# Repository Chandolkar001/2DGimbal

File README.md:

##  2DGimbal:

### Introduction
<p align="justify">This GitHub repository showcases a remarkable 3D-printed gimbal designed specifically for mobile photography enthusiasts. The gimbal's body is crafted using innovative 3D printing technology, resulting in a lightweight and durable structure. Additionally, the repository highlights an in-house developed PCB board, engineered to provide optimal performance and seamless integration with the gimbal system. Delve into the repository to access detailed resources, including 3D printing files, PCB design specifications, and code samples, empowering you to construct your own customized mobile photography gimbal with ease. Capture stunning, shake-free visuals using this impressive blend of 3D printing and PCB technology.</p>

### Block diagram
<br>
<p align="center"></img></p>

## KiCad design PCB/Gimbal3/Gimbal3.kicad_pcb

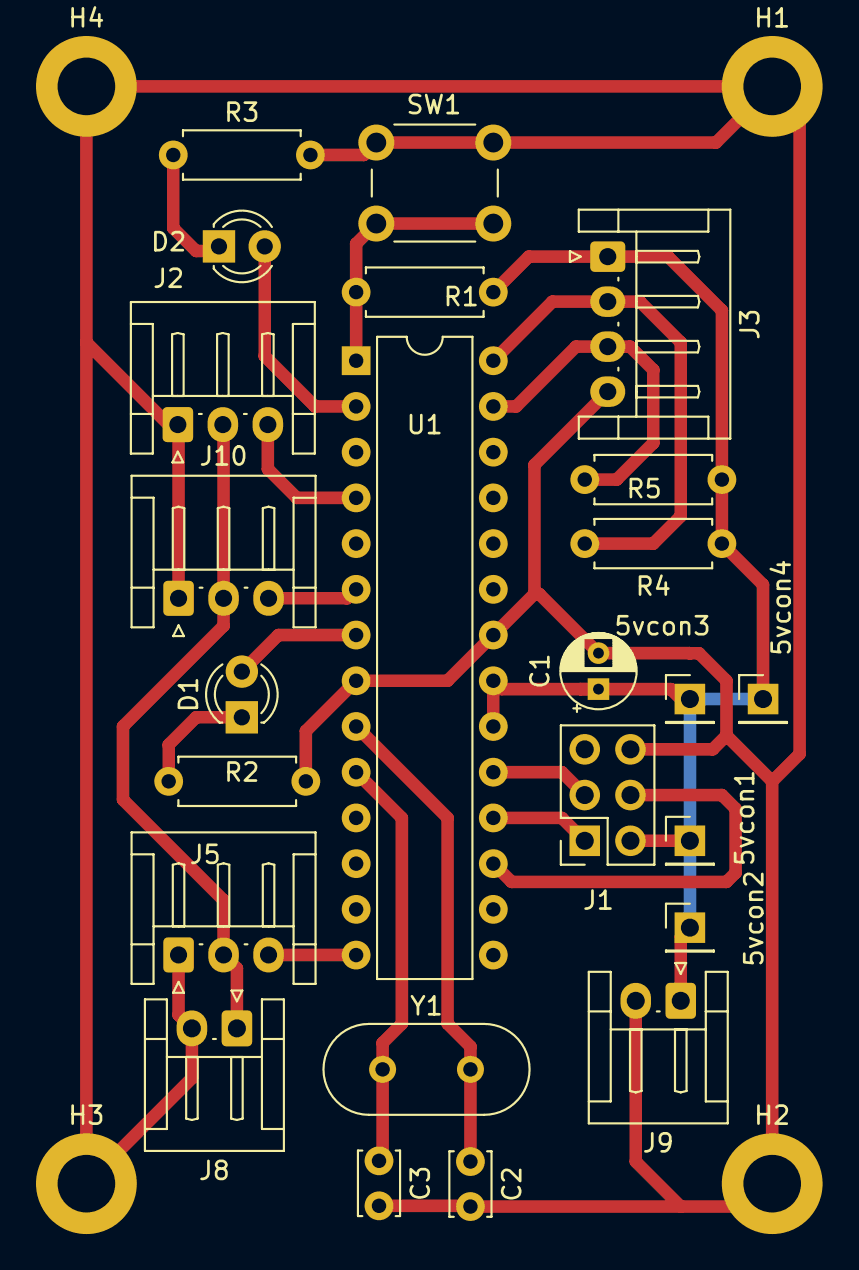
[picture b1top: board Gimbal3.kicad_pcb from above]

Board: 2 copper layers, 28 parts (0 on the bottom side), 16 nets.

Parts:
5vcon1, 5vcon2, 5vcon3, 5vcon4: Conn_01x01_Pin; PinHeader_1x01_P2.54mm_Vertical
C1: 10uF; CP_Radial_D4.0mm_P2.00mm
C2, C3: 22pF; C_Disc_D3.4mm_W2.1mm_P2.50mm
D1: POWER; LED_D3.0mm
D2: BUILD-IN; LED_D3.0mm
H1, H2, H3, H4: M3; MountingHole_3.2mm_M3_DIN965_Pad
J1: ISP; PinSocket_2x03_P2.54mm_Vertical
J2: Servo_M1; JST_EH_S3B-EH_1x03_P2.50mm_Horizontal
J3: I2C; JST_EH_S4B-EH_1x04_P2.50mm_Horizontal
J5: Servo_M2; JST_EH_S3B-EH_1x03_P2.50mm_Horizontal
J8: servo_power; JST_EH_S2B-EH_1x02_P2.50mm_Horizontal
J9: atmega_power; JST_EH_S2B-EH_1x02_P2.50mm_Horizontal
J10: Servo_M3; JST_EH_S3B-EH_1x03_P2.50mm_Horizontal
R1: 10K; R_Axial_DIN0207_L6.3mm_D2.5mm_P7.62mm_Horizontal
R2: 1K; R_Axial_DIN0207_L6.3mm_D2.5mm_P7.62mm_Horizontal
R3: 470E; R_Axial_DIN0207_L6.3mm_D2.5mm_P7.62mm_Horizontal
R4, R5: 4.7K; R_Axial_DIN0207_L6.3mm_D2.5mm_P7.62mm_Horizontal
SW1: reset; SW_PUSH_6mm
U1: ATmega328-P; DIP-28_W7.62mm
Y1: 16Mhz; Crystal_HC49-4H_Vertical

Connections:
+5V: 5vcon1.1, 5vcon2.1, 5vcon3.1, 5vcon4.1, C1.1, D1.2 (A), J1.2, J2.2, J3.1, J5.2, J8.1, J9.1, J10.2, R1.1, R4.1, R5.1, U1.7 (VCC), U1.20 (AVCC), U1.21 (AREF)
/LED: D2.2 (A), U1.2 (PD0)
/MISO: J1.1, U1.18 (PB4)
/MOSI: J1.4, U1.17 (PB3)
/RST1: R1.2, SW1.1, U1.1 (~RESET/PC6)
/SCK: J1.3, U1.19 (PB5)
/SCL: J3.2, R4.2, U1.28 (PC5)
/SDA: J3.3, R5.2, U1.27 (PC4)
/m1_sig: J2.3, U1.4 (PD2)
/m3_sig: J10.3, U1.6 (PD4)
GND: C1.2, C2.2, C3.2, H1.1, H2.1, H3.1, H4.1, J1.6, J2.1, J3.4, J5.1, J8.2, J9.2, J10.1, R2.2, R3.2, SW1.2, U1.8 (GND), U1.22 (GND)
unnamed: D1.1 (K), R2.1
unnamed: D2.1 (K), R3.1
unnamed: J5.3, U1.14 (PB0)
unnamed: C2.1, U1.9 (XTAL1/PB6), Y1.2
unnamed: C3.1, U1.10 (XTAL2/PB7), Y1.1

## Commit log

2023-05-27 gimbal
